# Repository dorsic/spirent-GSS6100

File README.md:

# Spirent GSS6100
Control programs and resources for the Spirent GSS6100 L1 GPS simulator device of one space vehicle.

## What you can do

With Spirent GSS6100 you can generate the signal of one GPS Satellite. You can test your GPS receiver front end sensitity by changing the signal level or measure the signal hardware delay.

## Internals

DSUB connectors

10MHz OCXO

Custom DSUB adapter to SMA

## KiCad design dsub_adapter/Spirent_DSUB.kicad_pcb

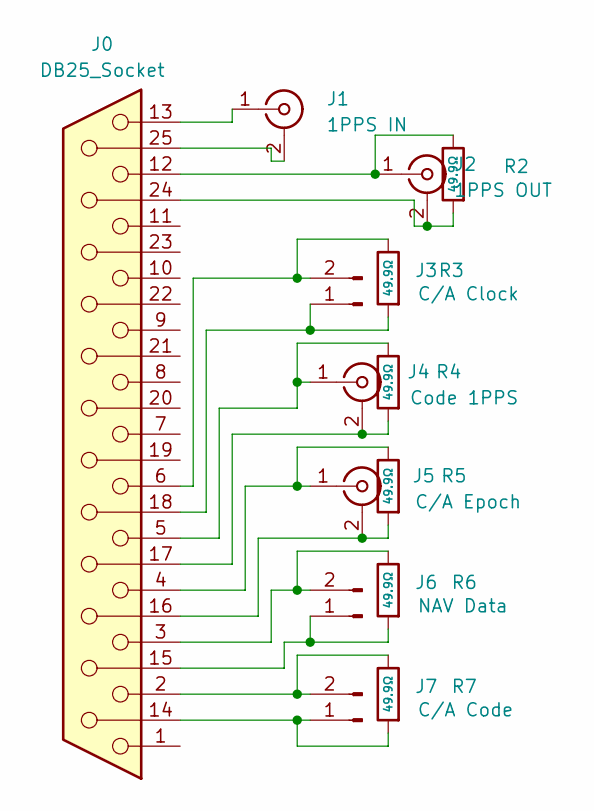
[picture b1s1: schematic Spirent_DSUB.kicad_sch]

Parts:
J0: DB25_Socket; DSUB-25_Socket_EdgeMount_P2.77mm
J1: 1PPS IN; SMA_Molex_73251-1153_EdgeMount_Horizontal
J2: 1PPS OUT; SMA_Molex_73251-1153_EdgeMount_Horizontal
J3: C/A Clock; PinHeader_1x02_P2.54mm_Vertical
J4: Code 1PPS; SMA_Molex_73251-1153_EdgeMount_Horizontal
J5: C/A Epoch; SMA_Molex_73251-1153_EdgeMount_Horizontal
J6: NAV Data; PinHeader_1x02_P2.54mm_Vertical
J7: C/A Code; PinHeader_1x02_P2.54mm_Vertical
R2, R3, R4, R5, R6, R7: 49.9Ω; R_0805; Overload Voltage (Max) 150V; Tolerance ±1%; Part 0805W8F499JT5E; LCSC C17720

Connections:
unnamed: J0.14, J7.1, R7.1
unnamed: J0.15, J6.1, R6.1
unnamed: J0.16, J5.2 (Ext), R5.1
unnamed: J0.17, J4.2 (Ext), R4.1
unnamed: J0.18, J3.1, R3.1
unnamed: J0.24, J2.2 (Ext), R2.1
unnamed: J0.25, J1.2 (Ext)
unnamed: J0.13, J1.1 (In)
unnamed: J0.12, J2.1 (In), R2.2
unnamed: J0.6, J3.2, R3.2
unnamed: J0.5, J4.1 (In), R4.2
unnamed: J0.4, J5.1 (In), R5.2
unnamed: J0.3, J6.2, R6.2
unnamed: J0.2, J7.2, R7.2

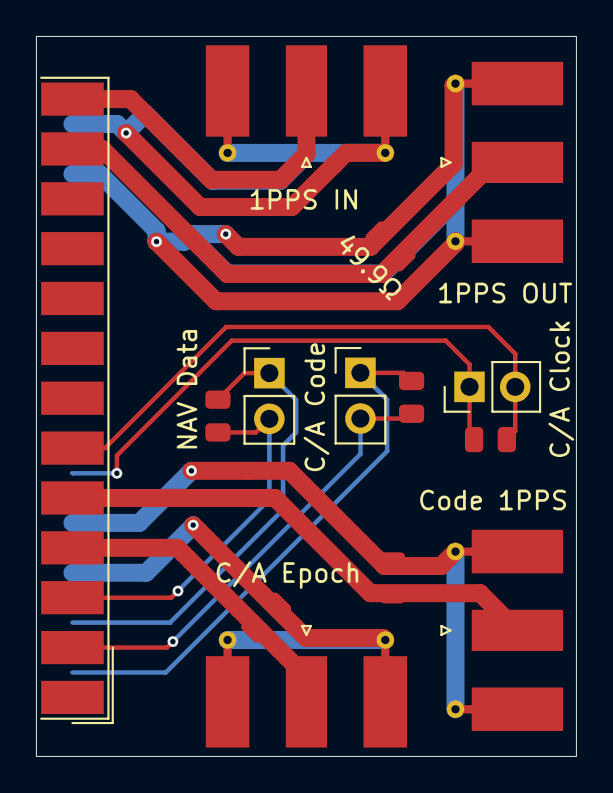
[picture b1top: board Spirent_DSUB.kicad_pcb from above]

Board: 2 copper layers, 30.0 x 40.0 mm, 14 parts (0 on the bottom side), 14 nets.

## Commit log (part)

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2026-03-28 Implement GSS6100 USB communication class
    With the help of ChatGPT.
2026-03-28 Add test script for GSS6100 device queries
    Implement a script to query and modify GSS6100 device parameters.
2026-03-28 Add USB interface imports to gss6100.py
2026-03-28 Enhance README with details on Spirent GSS6100
    Expanded README with additional sections on capabilities and internals.
